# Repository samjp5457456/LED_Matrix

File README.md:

# LED_Matrix
Repo for all files used in the LED Matrix project. This includes hardware files (schematics, Gerbers, and CAD files...) as well as software (GUI and functional code).

Created by Eleanor Taylor for the LED Matrix senior project (fall 2023) at UCCS.

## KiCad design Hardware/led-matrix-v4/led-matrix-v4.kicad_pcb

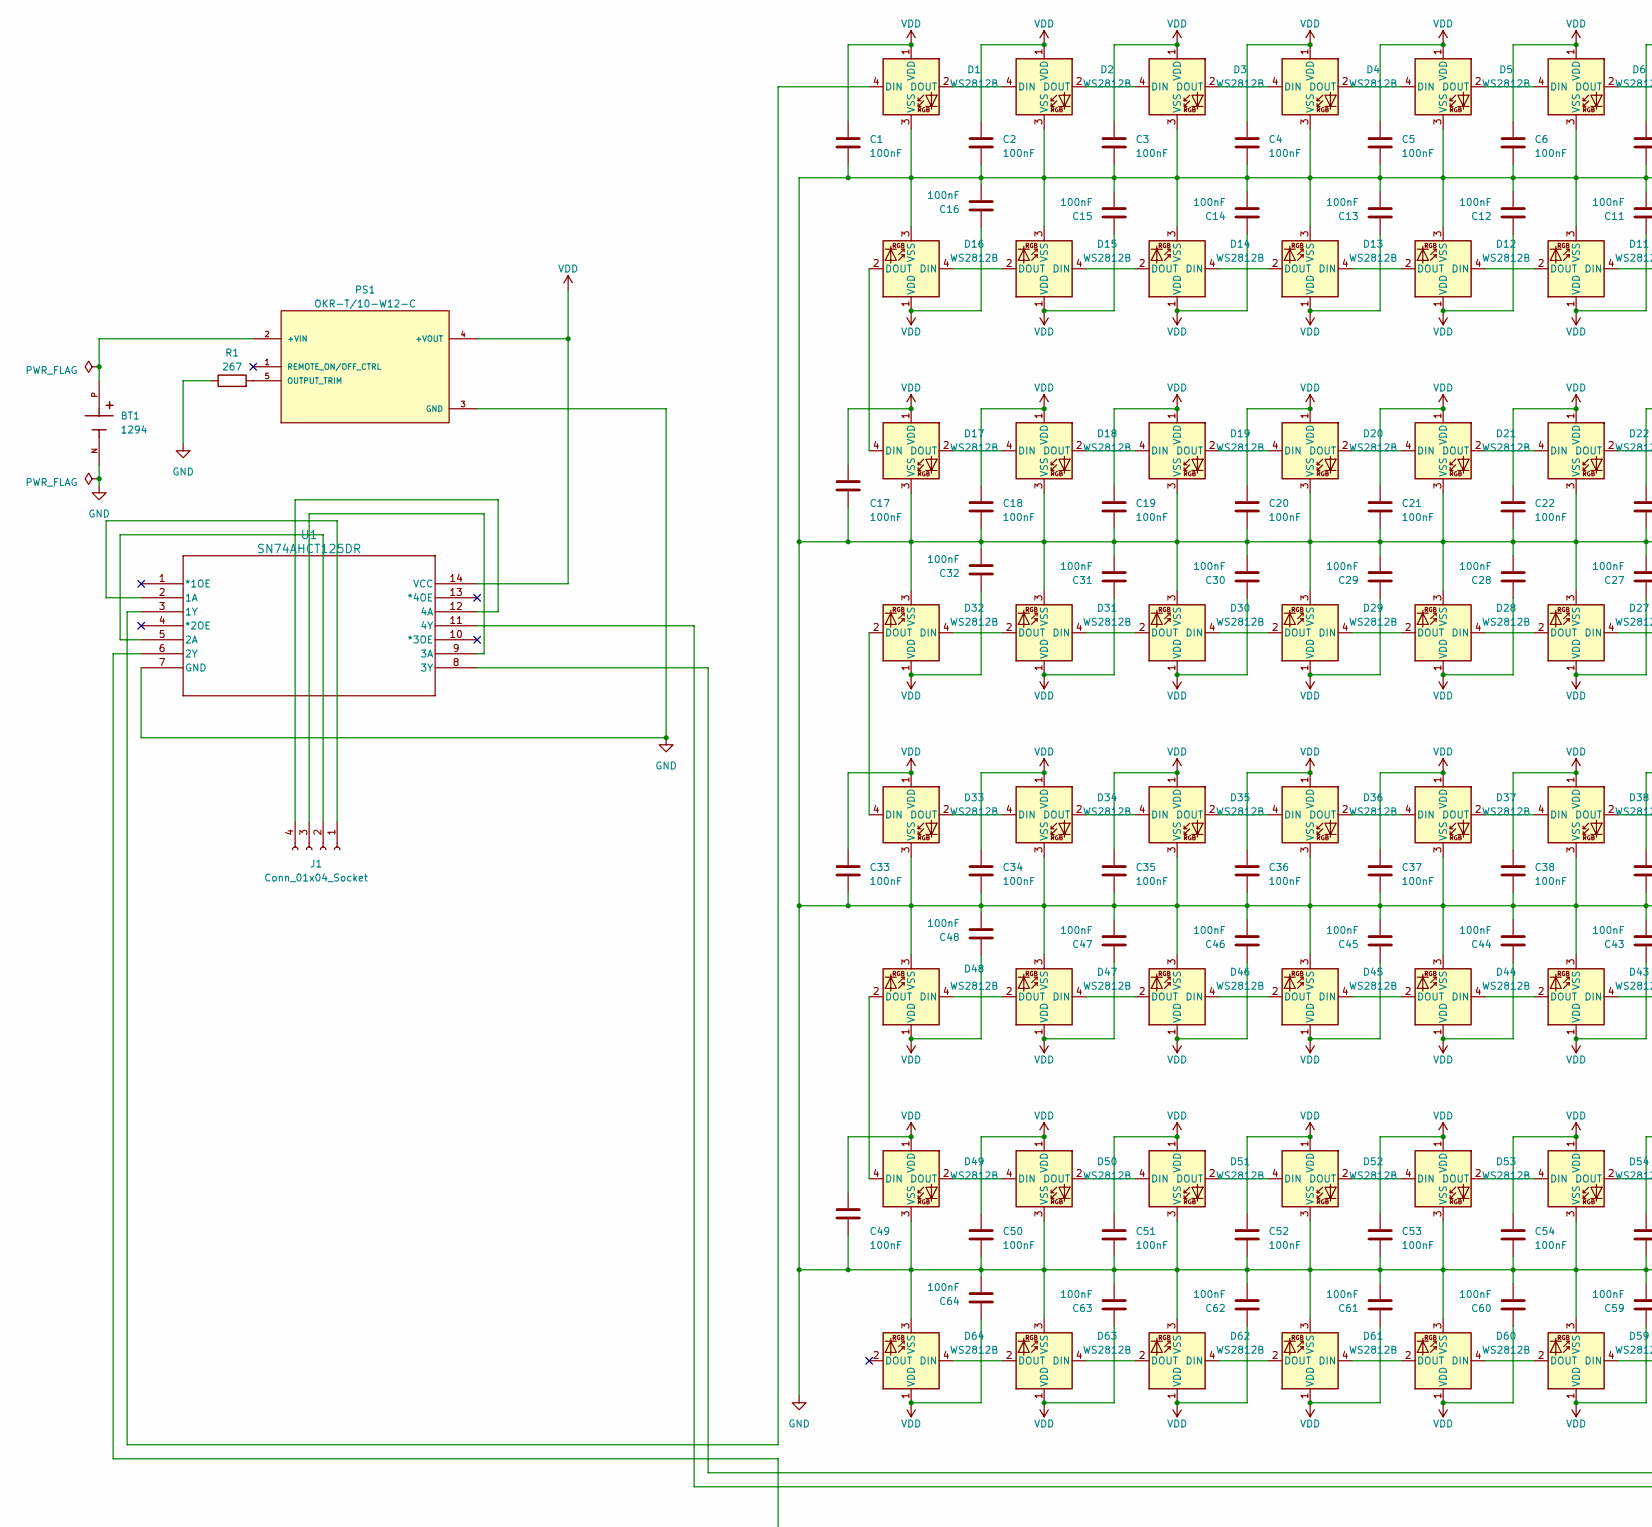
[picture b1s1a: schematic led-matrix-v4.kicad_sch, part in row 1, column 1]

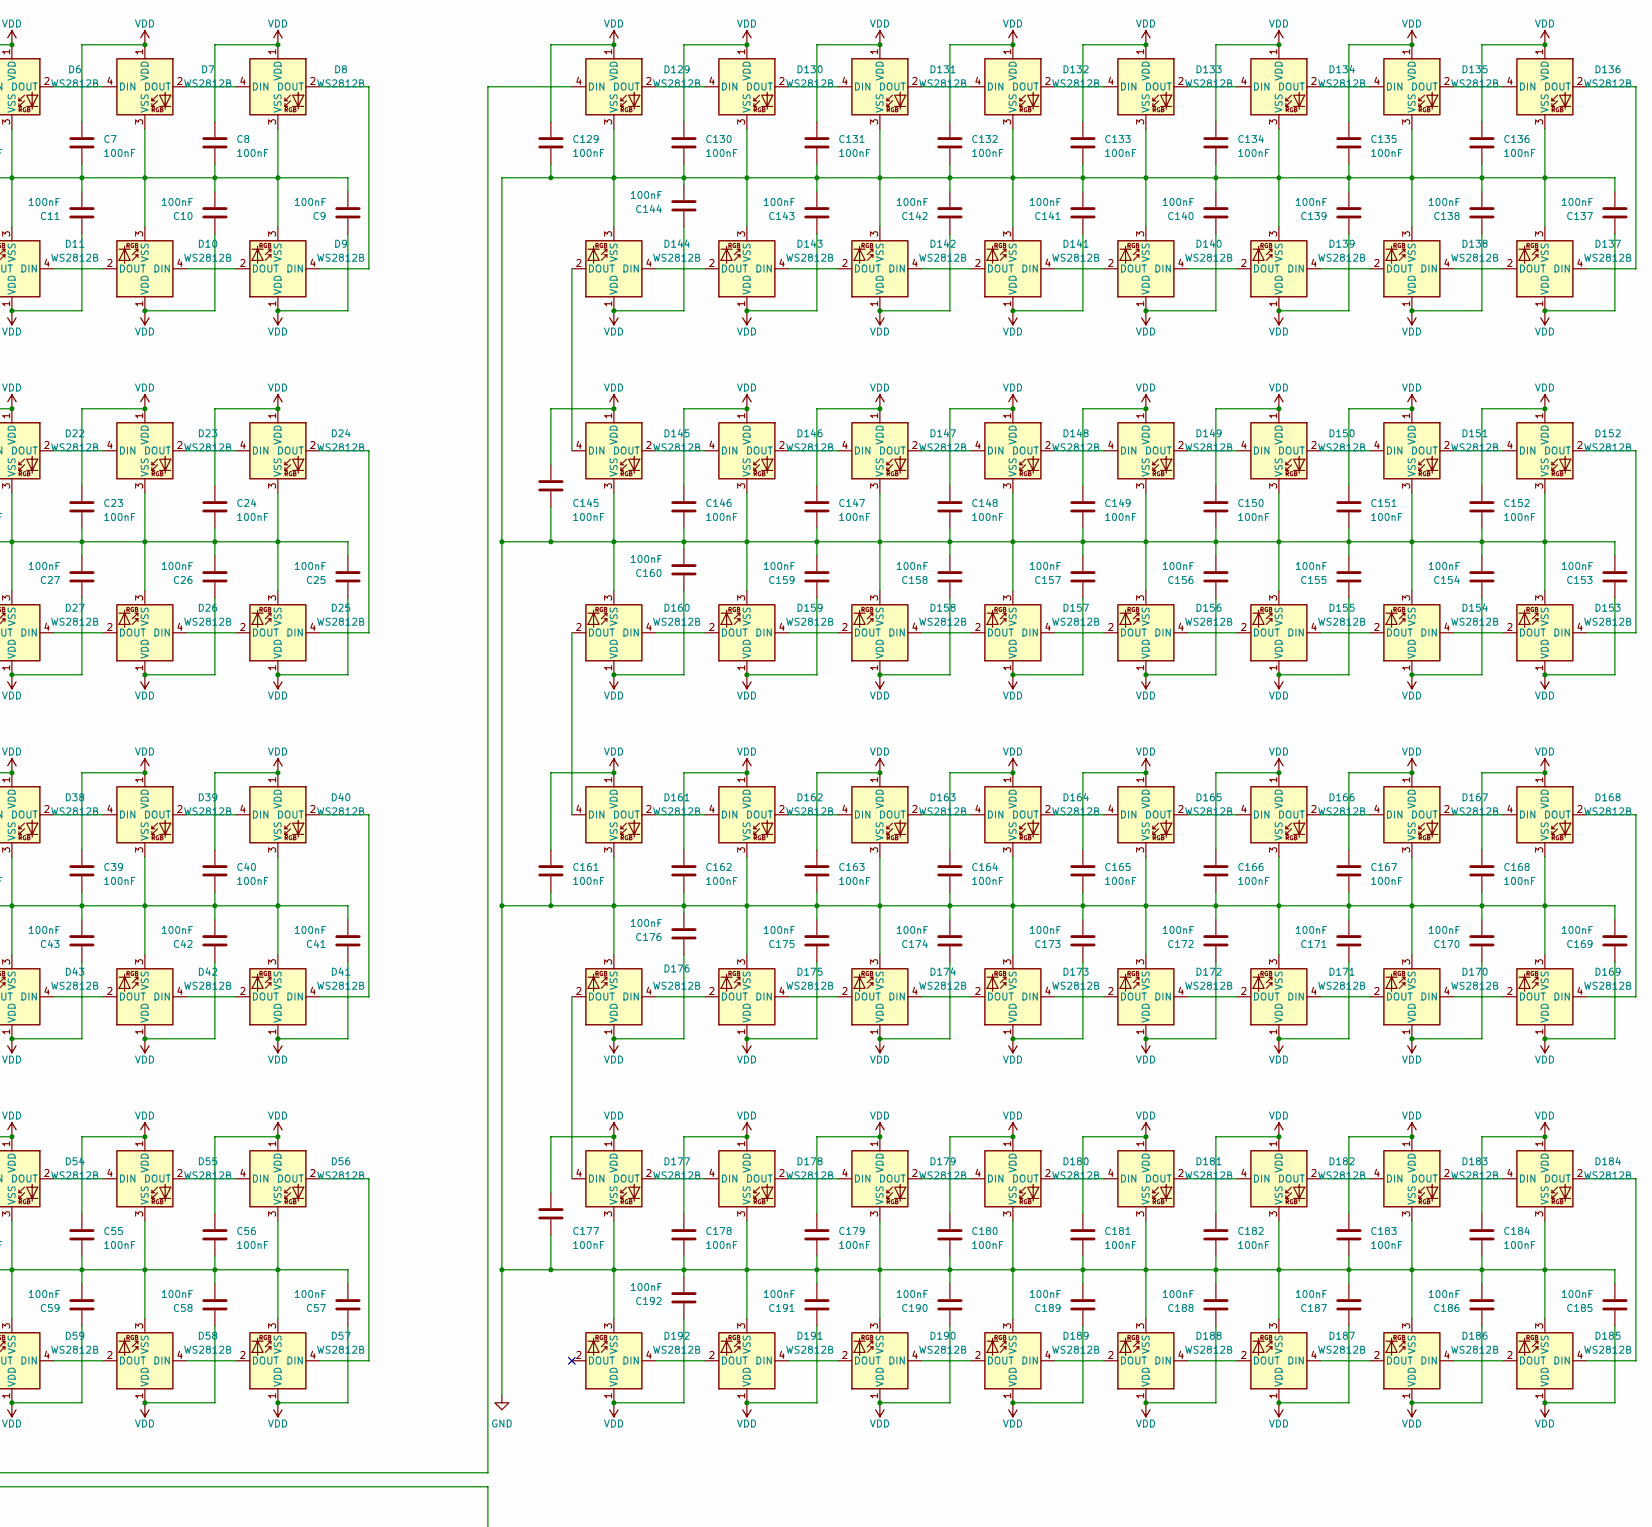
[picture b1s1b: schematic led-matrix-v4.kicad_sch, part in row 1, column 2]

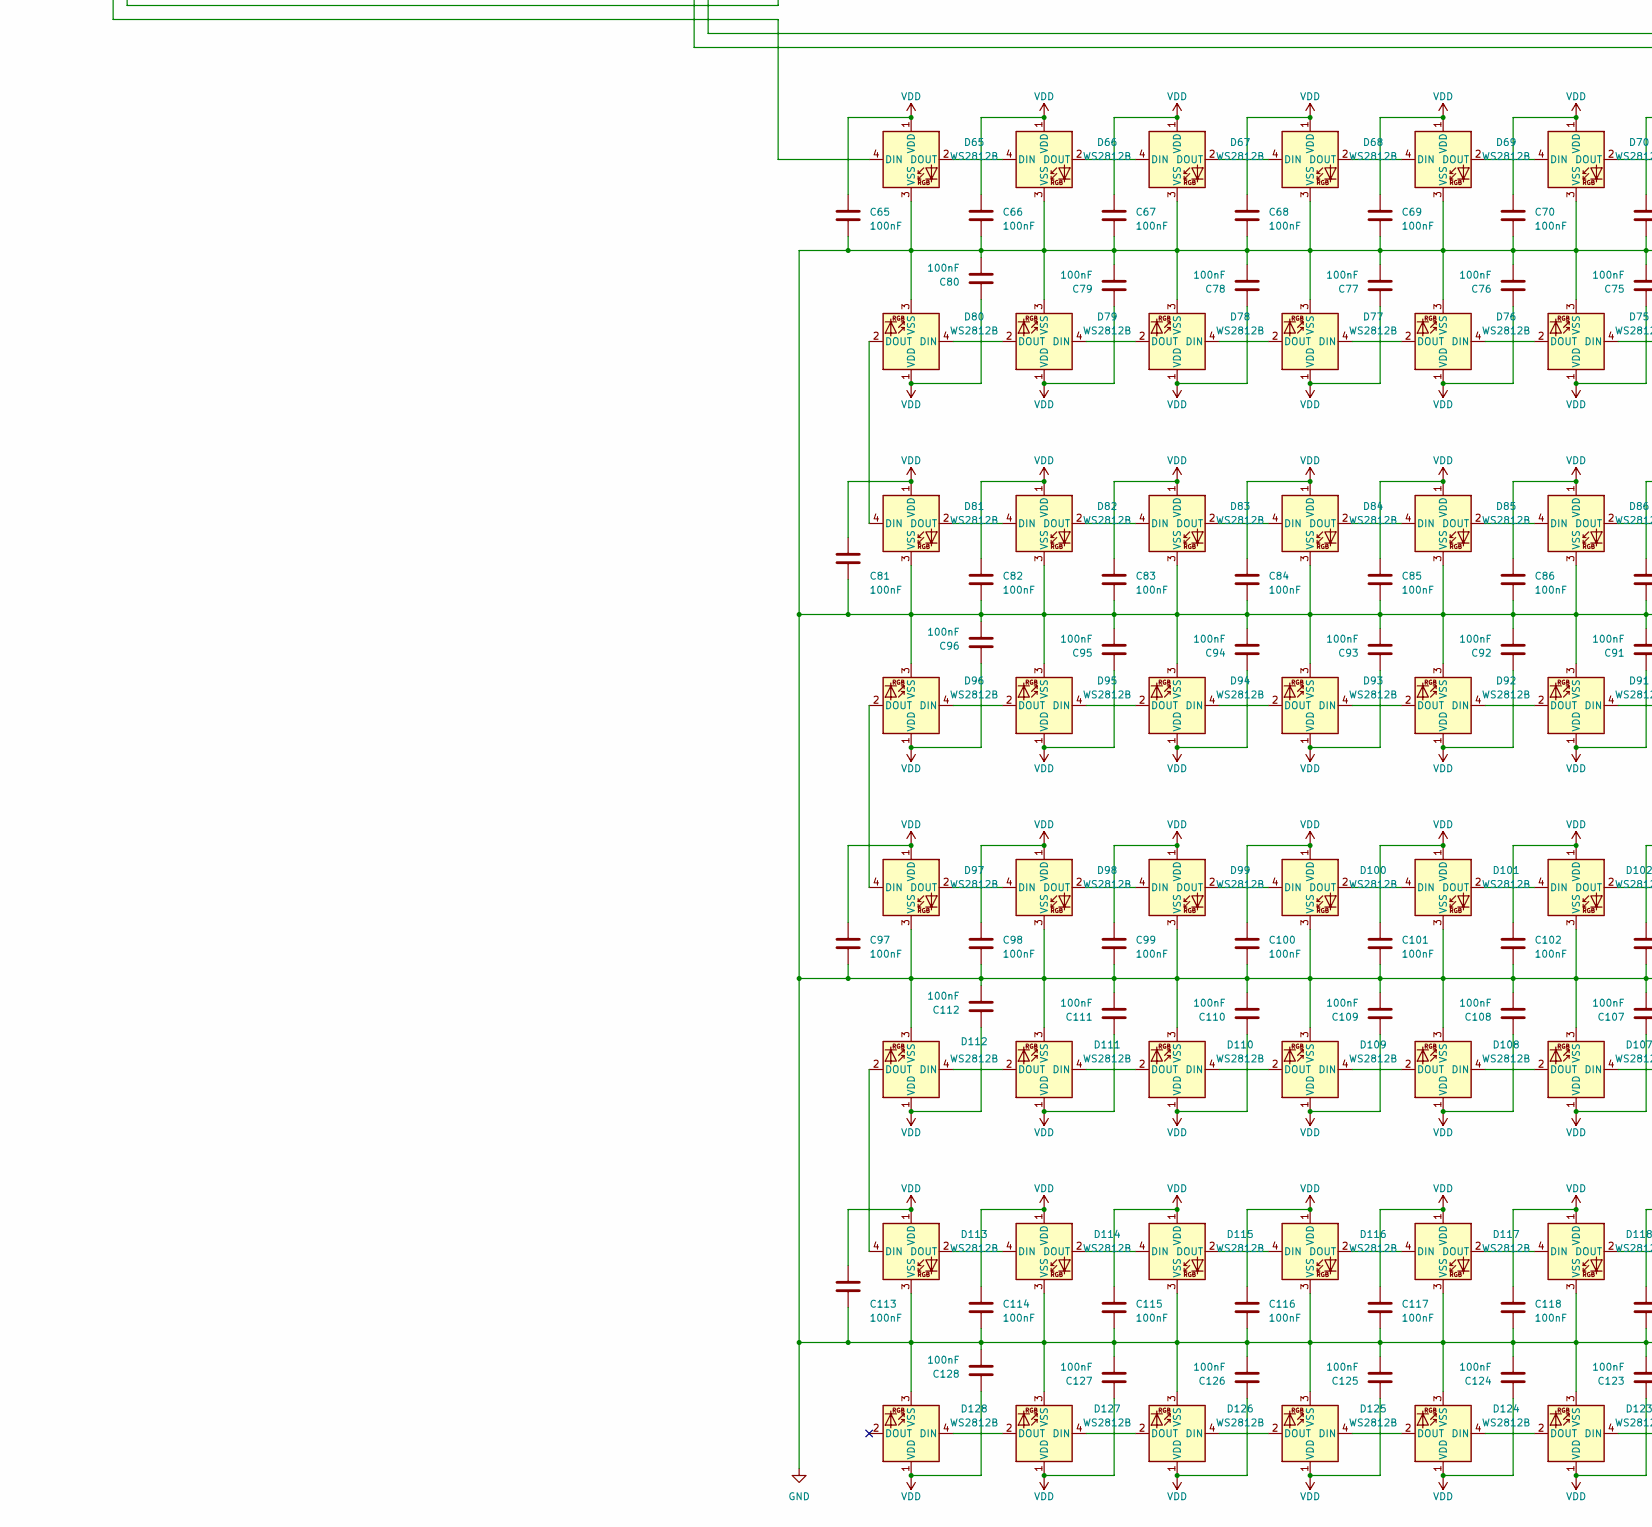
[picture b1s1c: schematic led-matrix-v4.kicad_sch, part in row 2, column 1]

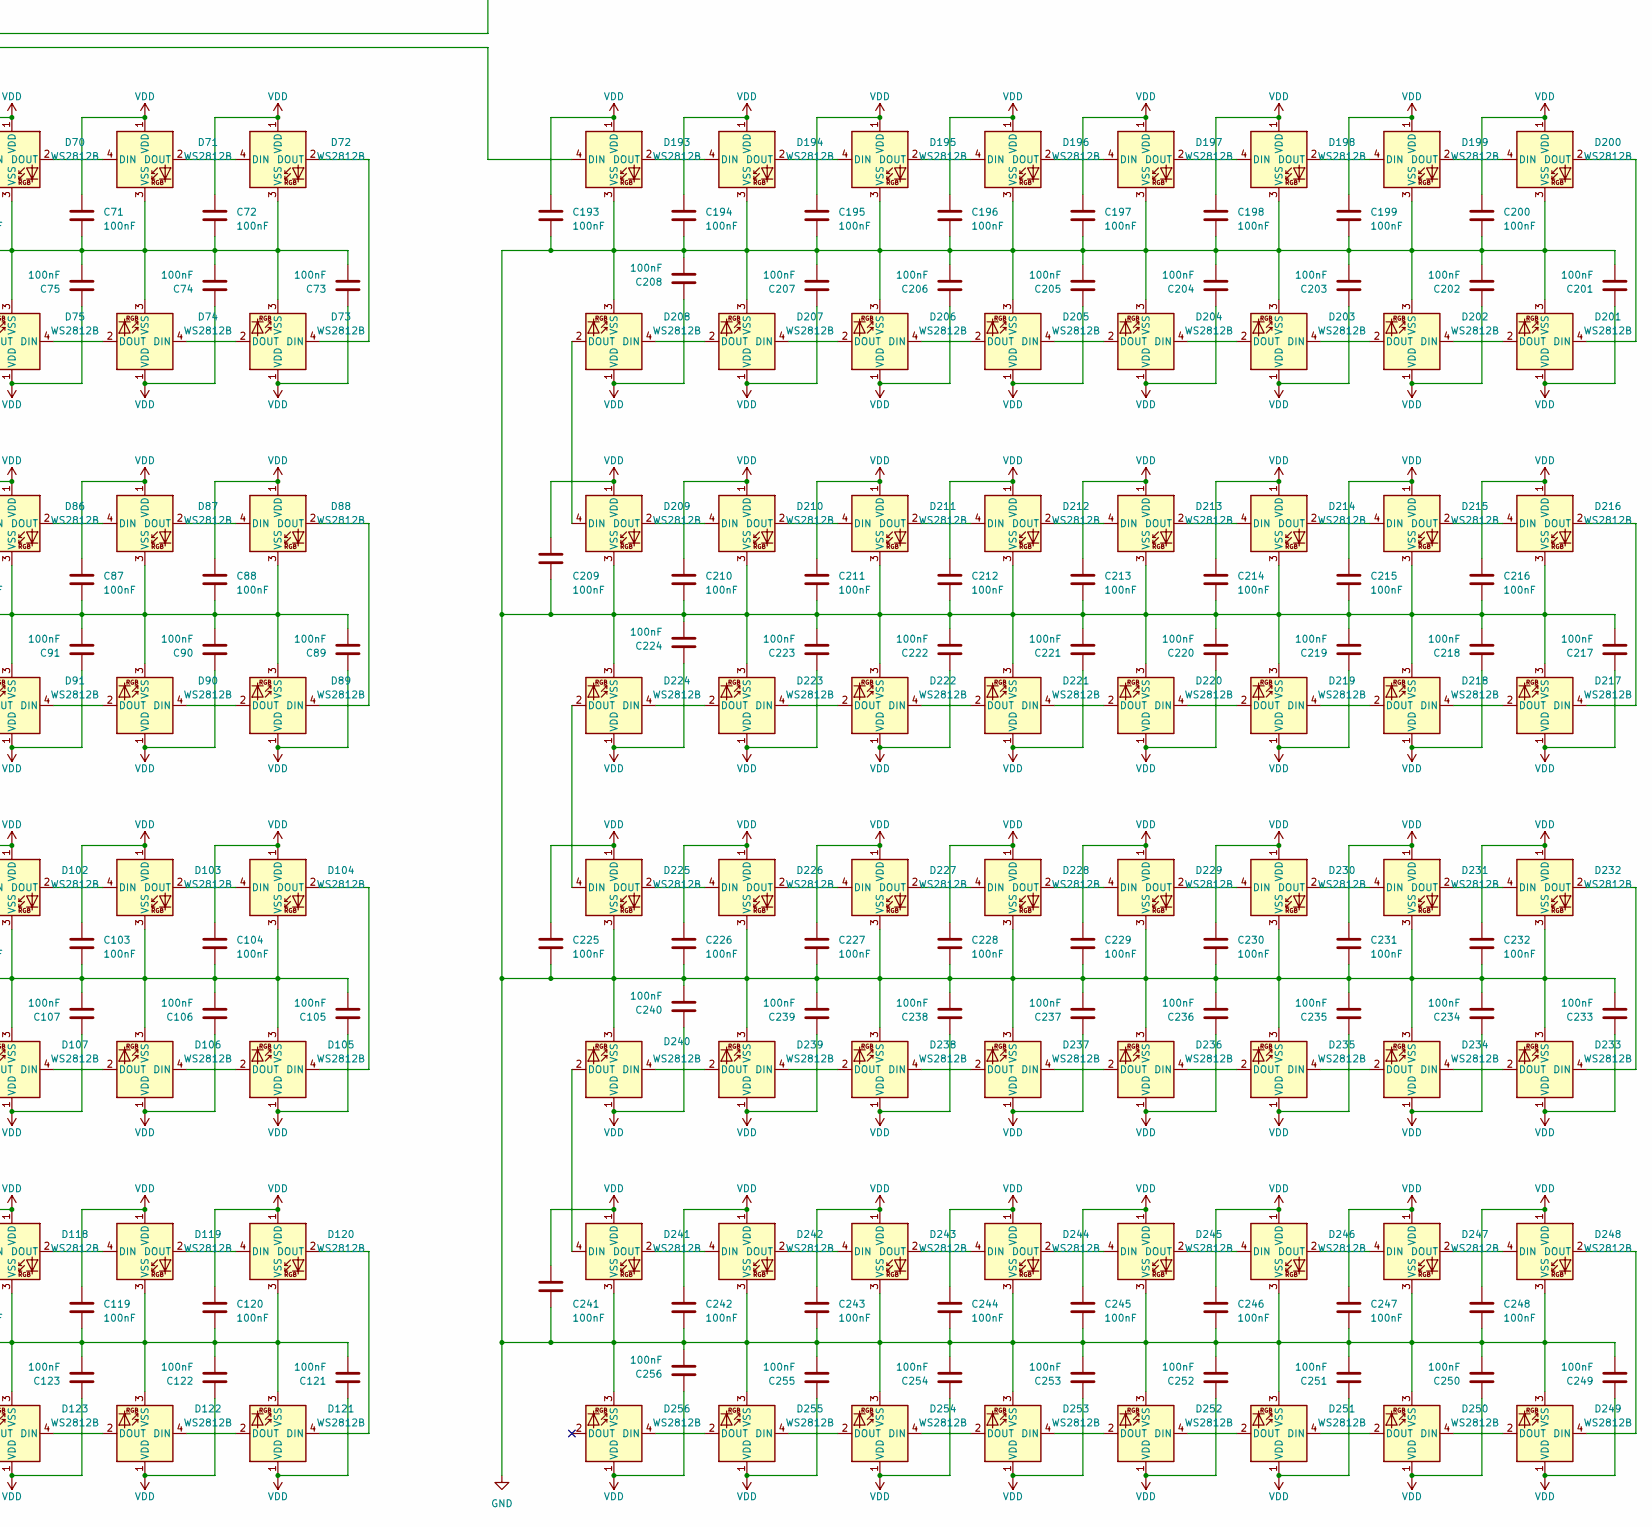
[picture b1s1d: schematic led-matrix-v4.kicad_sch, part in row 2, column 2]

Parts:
BT1: 1294; BAT_1294; PARTREV C
C1, C2, C3, C4, C5, C6, C7, C8, C9, C10, C11, C12, C13, C14, C15, C16, C17, C18, C19, C20, C21, C22, C23, C24, C25, C26, C27, C28, C29, C30, C31, C32, C33, C34, C35, C36, C37, C38, C39, C40, C41, C42, C43, C44, C45, C46, C47, C48, C49, C50, C51, C52, C53, C54, C55, C56, C57, C58, C59, C60, C61, C62, C63, C64, C65, C66, C67, C68, C69, C70, C71, C72, C73, C74, C75, C76, C77, C78, C79, C80, C81, C82, C83, C84, C85, C86, C87, C88, C89, C90, C91, C92, C93, C94, C95, C96, C97, C98, C99, C100, C101, C102, C103, C104, C105, C106, C107, C108, C109, C110, C111, C112, C113, C114, C115, C116, C117, C118, C119, C120, C121, C122, C123, C124, C125, C126, C127, C128, C129, C130, C131, C132, C133, C134, C135, C136, C137, C138, C139, C140, C141, C142, C143, C144, C145, C146, C147, C148, C149, C150, C151, C152, C153, C154, C155, C156, C157, C158, C159, C160, C161, C162, C163, C164, C165, C166, C167, C168, C169, C170, C171, C172, C173, C174, C175, C176, C177, C178, C179, C180, C181, C182, C183, C184, C185, C186, C187, C188, C189, C190, C191, C192, C193, C194, C195, C196, C197, C198, C199, C200, C201, C202, C203, C204, C205, C206, C207, C208, C209, C210, C211, C212, C213, C214, C215, C216, C217, C218, C219, C220, C221, C222, C223, C224, C225, C226, C227, C228, C229, C230, C231, C232, C233, C234, C235, C236, C237, C238, C239, C240, C241, C242, C243, C244, C245, C246, C247, C248, C249, C250, C251, C252, C253, C254, C255, C256: 100nF; C_0805_2012Metric
D1, D2, D3, D4, D5, D6, D7, D8, D9, D10, D11, D12, D13, D14, D15, D16, D17, D18, D19, D20, D21, D22, D23, D24, D25, D26, D27, D28, D29, D30, D31, D32, D33, D34, D35, D36, D37, D38, D39, D40, D41, D42, D43, D44, D45, D46, D47, D48, D49, D50, D51, D52, D53, D54, D55, D56, D57, D58, D59, D60, D61, D62, D63, D64, D65, D66, D67, D68, D69, D70, D71, D72, D73, D74, D75, D76, D77, D78, D79, D80, D81, D82, D83, D84, D85, D86, D87, D88, D89, D90, D91, D92, D93, D94, D95, D96, D97, D98, D99, D100, D101, D102, D103, D104, D105, D106, D107, D108, D109, D110, D111, D112, D113, D114, D115, D116, D117, D118, D119, D120, D121, D122, D123, D124, D125, D126, D127, D128, D129, D130, D131, D132, D133, D134, D135, D136, D137, D138, D139, D140, D141, D142, D143, D144, D145, D146, D147, D148, D149, D150, D151, D152, D153, D154, D155, D156, D157, D158, D159, D160, D161, D162, D163, D164, D165, D166, D167, D168, D169, D170, D171, D172, D173, D174, D175, D176, D177, D178, D179, D180, D181, D182, D183, D184, D185, D186, D187, D188, D189, D190, D191, D192, D193, D194, D195, D196, D197, D198, D199, D200, D201, D202, D203, D204, D205, D206, D207, D208, D209, D210, D211, D212, D213, D214, D215, D216, D217, D218, D219, D220, D221, D222, D223, D224, D225, D226, D227, D228, D229, D230, D231, D232, D233, D234, D235, D236, D237, D238, D239, D240, D241, D242, D243, D244, D245, D246, D247, D248, D249, D250, D251, D252, D253, D254, D255, D256: WS2812B; LED_WS2812B_PLCC4_5.0x5.0mm_P3.2mm
J1: Conn_01x04_Socket; PinHeader_1x04_P2.54mm_Vertical
PS1: OKR-T/10-W12-C; CONV_OKR-T_10-W12-C
R1: 267; R_0805_2012Metric
U1: SN74AHCT125DR; D14

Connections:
GND: BT1.N, C1.2, C2.2, C3.2, C4.2, C5.2, C6.2, C7.2, C8.2, C9.2, C10.2, C11.2, C12.2, C13.2, C14.2, C15.2, C16.2, C17.2, C18.2, C19.2, C20.2, C21.2, C22.2, C23.2, C24.2, C25.2, C26.2, C27.2, C28.2, C29.2, C30.2, C31.2, C32.2, C33.2, C34.2, C35.2, C36.2, C37.2, C38.2, C39.2, C40.2, C41.2, C42.2, C43.2, C44.2, C45.2, C46.2, C47.2, C48.2, C49.2, C50.2, C51.2, C52.2, C53.2, C54.2, C55.2, C56.2, C57.2, C58.2, C59.2, C60.2, C61.2, C62.2, C63.2, C64.2, C65.2, C66.2, C67.2, C68.2, C69.2, C70.2, C71.2, C72.2, C73.2, C74.2, C75.2, C76.2, C77.2, C78.2, C79.2, C80.2, C81.2, C82.2, C83.2, C84.2, C85.2, C86.2, C87.2, C88.2, C89.2, C90.2, C91.2, C92.2, C93.2, C94.2, C95.2, C96.2, C97.2, C98.2, C99.2, C100.2, C101.2, C102.2, C103.2, C104.2, C105.2, C106.2, C107.2, C108.2, C109.2, C110.2, C111.2, C112.2, C113.2, C114.2, C115.2, C116.2, C117.2, C118.2, C119.2, C120.2, C121.2, C122.2, C123.2, C124.2, C125.2, C126.2, C127.2, C128.2, C129.2, C130.2, C131.2, C132.2, C133.2, C134.2, C135.2, C136.2, C137.2, C138.2, C139.2, C140.2, C141.2, C142.2, C143.2, C144.2, C145.2, C146.2, C147.2, C148.2, C149.2, C150.2, C151.2, C152.2, C153.2, C154.2, C155.2, C156.2, C157.2, C158.2, C159.2, C160.2, C161.2, C162.2, C163.2, C164.2, C165.2, C166.2, C167.2, C168.2, C169.2, C170.2, C171.2, C172.2, C173.2, C174.2, C175.2, C176.2, C177.2, C178.2, C179.2, C180.2, C181.2, C182.2, C183.2, C184.2, C185.2, C186.2, C187.2, C188.2, C189.2, C190.2, C191.2, C192.2, C193.2, C194.2, C195.2, C196.2, C197.2, C198.2, C199.2, C200.2, C201.2, C202.2, C203.2, C204.2, C205.2, C206.2, C207.2, C208.2, C209.2, C210.2, C211.2, C212.2, C213.2, C214.2, C215.2, C216.2, C217.2, C218.2, C219.2, C220.2, C221.2, C222.2, C223.2, C224.2, C225.2, C226.2, C227.2, C228.2, C229.2, C230.2, C231.2, C232.2, C233.2, C234.2, C235.2, C236.2, C237.2, C238.2, C239.2, C240.2, C241.2, C242.2, C243.2, C244.2, C245.2, C246.2, C247.2, C248.2, C249.2, C250.2, C251.2, C252.2, C253.2, C254.2, C255.2, C256.2, D1.3 (VSS), D2.3 (VSS), D3.3 (VSS), D4.3 (VSS), D5.3 (VSS), D6.3 (VSS), D7.3 (VSS), D8.3 (VSS), D9.3 (VSS), D10.3 (VSS), D11.3 (VSS), D12.3 (VSS), D13.3 (VSS), D14.3 (VSS), D15.3 (VSS), D16.3 (VSS), D17.3 (VSS), D18.3 (VSS), D19.3 (VSS), D20.3 (VSS), D21.3 (VSS), D22.3 (VSS), D23.3 (VSS), D24.3 (VSS), D25.3 (VSS), D26.3 (VSS), D27.3 (VSS), D28.3 (VSS), D29.3 (VSS), D30.3 (VSS), D31.3 (VSS), D32.3 (VSS), D33.3 (VSS), D34.3 (VSS), D35.3 (VSS), D36.3 (VSS), D37.3 (VSS), D38.3 (VSS), D39.3 (VSS), D40.3 (VSS), D41.3 (VSS), D42.3 (VSS), D43.3 (VSS), D44.3 (VSS), D45.3 (VSS), D46.3 (VSS), D47.3 (VSS), D48.3 (VSS), D49.3 (VSS), D50.3 (VSS), D51.3 (VSS), D52.3 (VSS), D53.3 (VSS), D54.3 (VSS), D55.3 (VSS), D56.3 (VSS), D57.3 (VSS), D58.3 (VSS), D59.3 (VSS), D60.3 (VSS), D61.3 (VSS), D62.3 (VSS), D63.3 (VSS), D64.3 (VSS), D65.3 (VSS), D66.3 (VSS), D67.3 (VSS), D68.3 (VSS), D69.3 (VSS), D70.3 (VSS), D71.3 (VSS), D72.3 (VSS), D73.3 (VSS), D74.3 (VSS), D75.3 (VSS), D76.3 (VSS), D77.3 (VSS)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
unnamed: D1.4 (DIN), U1.3 (1Y)
unnamed: D1.2 (DOUT), D2.4 (DIN)
unnamed: D2.2 (DOUT), D3.4 (DIN)
unnamed: D3.2 (DOUT), D4.4 (DIN)
unnamed: D4.2 (DOUT), D5.4 (DIN)
unnamed: D5.2 (DOUT), D6.4 (DIN)
unnamed: D6.2 (DOUT), D7.4 (DIN)
unnamed: D7.2 (DOUT), D8.4 (DIN)
unnamed: D8.2 (DOUT), D9.4 (DIN)
unnamed: D9.2 (DOUT), D10.4 (DIN)
unnamed: D10.2 (DOUT), D11.4 (DIN)
unnamed: D11.2 (DOUT), D12.4 (DIN)
unnamed: D12.2 (DOUT), D13.4 (DIN)
unnamed: D13.2 (DOUT), D14.4 (DIN)
unnamed: D14.2 (DOUT), D15.4 (DIN)
unnamed: D15.2 (DOUT), D16.4 (DIN)
unnamed: D16.2 (DOUT), D17.4 (DIN)
unnamed: D17.2 (DOUT), D18.4 (DIN)
unnamed: D18.2 (DOUT), D19.4 (DIN)
unnamed: D19.2 (DOUT), D20.4 (DIN)
unnamed: D20.2 (DOUT), D21.4 (DIN)
unnamed: D21.2 (DOUT), D22.4 (DIN)
unnamed: D22.2 (DOUT), D23.4 (DIN)
unnamed: D23.2 (DOUT), D24.4 (DIN)
unnamed: D24.2 (DOUT), D25.4 (DIN)
unnamed: D25.2 (DOUT), D26.4 (DIN)
unnamed: D26.2 (DOUT), D27.4 (DIN)
unnamed: D27.2 (DOUT), D28.4 (DIN)
unnamed: D28.2 (DOUT), D29.4 (DIN)
unnamed: D29.2 (DOUT), D30.4 (DIN)
unnamed: D30.2 (DOUT), D31.4 (DIN)
unnamed: D31.2 (DOUT), D32.4 (DIN)
unnamed: D32.2 (DOUT), D33.4 (DIN)
unnamed: D33.2 (DOUT), D34.4 (DIN)
unnamed: D34.2 (DOUT), D35.4 (DIN)
unnamed: D35.2 (DOUT), D36.4 (DIN)
unnamed: D36.2 (DOUT), D37.4 (DIN)
unnamed: D37.2 (DOUT), D38.4 (DIN)
unnamed: D38.2 (DOUT), D39.4 (DIN)
unnamed: D39.2 (DOUT), D40.4 (DIN)
unnamed: D40.2 (DOUT), D41.4 (DIN)
unnamed: D41.2 (DOUT), D42.4 (DIN)
unnamed: D42.2 (DOUT), D43.4 (DIN)
unnamed: D43.2 (DOUT), D44.4 (DIN)
unnamed: D44.2 (DOUT), D45.4 (DIN)
unnamed: D45.2 (DOUT), D46.4 (DIN)
unnamed: D46.2 (DOUT), D47.4 (DIN)
unnamed: D47.2 (DOUT), D48.4 (DIN)
unnamed: D48.2 (DOUT), D49.4 (DIN)
unnamed: D49.2 (DOUT), D50.4 (DIN)
unnamed: D50.2 (DOUT), D51.4 (DIN)
unnamed: D51.2 (DOUT), D52.4 (DIN)
unnamed: D52.2 (DOUT), D53.4 (DIN)
unnamed: D53.2 (DOUT), D54.4 (DIN)
unnamed: D54.2 (DOUT), D55.4 (DIN)
unnamed: D55.2 (DOUT), D56.4 (DIN)
unnamed: D56.2 (DOUT), D57.4 (DIN)
unnamed: D57.2 (DOUT), D58.4 (DIN)
unnamed: D58.2 (DOUT), D59.4 (DIN)
unnamed: D59.2 (DOUT), D60.4 (DIN)
unnamed: D60.2 (DOUT), D61.4 (DIN)
unnamed: D61.2 (DOUT), D62.4 (DIN)
unnamed: D62.2 (DOUT), D63.4 (DIN)
unnamed: D63.2 (DOUT), D64.4 (DIN)
unnamed: D65.4 (DIN), U1.6 (2Y)
unnamed: D65.2 (DOUT), D66.4 (DIN)
unnamed: D66.2 (DOUT), D67.4 (DIN)
unnamed: D67.2 (DOUT), D68.4 (DIN)
unnamed: D68.2 (DOUT), D69.4 (DIN)
unnamed: D69.2 (DOUT), D70.4 (DIN)
unnamed: D70.2 (DOUT), D71.4 (DIN)
unnamed: D71.2 (DOUT), D72.4 (DIN)
unnamed: D72.2 (DOUT), D73.4 (DIN)
unnamed: D73.2 (DOUT), D74.4 (DIN)
unnamed: D74.2 (DOUT), D75.4 (DIN)
unnamed: D75.2 (DOUT), D76.4 (DIN)
unnamed: D76.2 (DOUT), D77.4 (DIN)
unnamed: D77.2 (DOUT), D78.4 (DIN)
unnamed: D78.2 (DOUT), D79.4 (DIN)
unnamed: D79.2 (DOUT), D80.4 (DIN)
unnamed: D80.2 (DOUT), D81.4 (DIN)
unnamed: D81.2 (DOUT), D82.4 (DIN)
unnamed: D82.2 (DOUT), D83.4 (DIN)
unnamed: D83.2 (DOUT), D84.4 (DIN)
unnamed: D84.2 (DOUT), D85.4 (DIN)
unnamed: D85.2 (DOUT), D86.4 (DIN)
unnamed: D86.2 (DOUT), D87.4 (DIN)
unnamed: D87.2 (DOUT), D88.4 (DIN)
unnamed: D88.2 (DOUT), D89.4 (DIN)
unnamed: D89.2 (DOUT), D90.4 (DIN)
unnamed: D90.2 (DOUT), D91.4 (DIN)
unnamed: D91.2 (DOUT), D92.4 (DIN)
unnamed: D92.2 (DOUT), D93.4 (DIN)
unnamed: D93.2 (DOUT), D94.4 (DIN)
unnamed: D94.2 (DOUT), D95.4 (DIN)
unnamed: D95.2 (DOUT), D96.4 (DIN)
unnamed: D96.2 (DOUT), D97.4 (DIN)
unnamed: D97.2 (DOUT), D98.4 (DIN)
unnamed: D98.2 (DOUT), D99.4 (DIN)
unnamed: D99.2 (DOUT), D100.4 (DIN)
unnamed: D100.2 (DOUT), D101.4 (DIN)
unnamed: D101.2 (DOUT), D102.4 (DIN)
unnamed: D102.2 (DOUT), D103.4 (DIN)
unnamed: D103.2 (DOUT), D104.4 (DIN)
unnamed: D104.2 (DOUT), D105.4 (DIN)
unnamed: D105.2 (DOUT), D106.4 (DIN)
unnamed: D106.2 (DOUT), D107.4 (DIN)
unnamed: D107.2 (DOUT), D108.4 (DIN)
unnamed: D108.2 (DOUT), D109.4 (DIN)
unnamed: D109.2 (DOUT), D110.4 (DIN)
unnamed: D110.2 (DOUT), D111.4 (DIN)
unnamed: D111.2 (DOUT), D112.4 (DIN)
unnamed: D112.2 (DOUT), D113.4 (DIN)
unnamed: D113.2 (DOUT), D114.4 (DIN)
unnamed: D114.2 (DOUT), D115.4 (DIN)
unnamed: D115.2 (DOUT), D116.4 (DIN)
unnamed: D116.2 (DOUT), D117.4 (DIN)
unnamed: D117.2 (DOUT), D118.4 (DIN)
unnamed: D118.2 (DOUT), D119.4 (DIN)
unnamed: D119.2 (DOUT), D120.4 (DIN)
unnamed: D120.2 (DOUT), D121.4 (DIN)
unnamed: D121.2 (DOUT), D122.4 (DIN)
unnamed: D122.2 (DOUT), D123.4 (DIN)
unnamed: D123.2 (DOUT), D124.4 (DIN)
unnamed: D124.2 (DOUT), D125.4 (DIN)
unnamed: D125.2 (DOUT), D126.4 (DIN)
unnamed: D126.2 (DOUT), D127.4 (DIN)
unnamed: D127.2 (DOUT), D128.4 (DIN)
unnamed: D129.4 (DIN), U1.8 (3Y)
unnamed: D129.2 (DOUT), D130.4 (DIN)
unnamed: D130.2 (DOUT), D131.4 (DIN)
unnamed: D131.2 (DOUT), D132.4 (DIN)
unnamed: D132.2 (DOUT), D133.4 (DIN)
unnamed: D133.2 (DOUT), D134.4 (DIN)
unnamed: D134.2 (DOUT), D135.4 (DIN)
unnamed: D135.2 (DOUT), D136.4 (DIN)
unnamed: D136.2 (DOUT), D137.4 (DIN)
unnamed: D137.2 (DOUT), D138.4 (DIN)
unnamed: D138.2 (DOUT), D139.4 (DIN)
unnamed: D139.2 (DOUT), D140.4 (DIN)
unnamed: D140.2 (DOUT), D141.4 (DIN)
unnamed: D141.2 (DOUT), D142.4 (DIN)
unnamed: D142.2 (DOUT), D143.4 (DIN)
unnamed: D143.2 (DOUT), D144.4 (DIN)
unnamed: D144.2 (DOUT), D145.4 (DIN)
unnamed: D145.2 (DOUT), D146.4 (DIN)
unnamed: D146.2 (DOUT), D147.4 (DIN)
unnamed: D147.2 (DOUT), D148.4 (DIN)
unnamed: D148.2 (DOUT), D149.4 (DIN)
unnamed: D149.2 (DOUT), D150.4 (DIN)
unnamed: D150.2 (DOUT), D151.4 (DIN)
unnamed: D151.2 (DOUT), D152.4 (DIN)
unnamed: D152.2 (DOUT), D153.4 (DIN)
unnamed: D153.2 (DOUT), D154.4 (DIN)
unnamed: D154.2 (DOUT), D155.4 (DIN)
unnamed: D155.2 (DOUT), D156.4 (DIN)
unnamed: D156.2 (DOUT), D157.4 (DIN)
unnamed: D157.2 (DOUT), D158.4 (DIN)
unnamed: D158.2 (DOUT), D159.4 (DIN)
unnamed: D159.2 (DOUT), D160.4 (DIN)
unnamed: D160.2 (DOUT), D161.4 (DIN)
unnamed: D161.2 (DOUT), D162.4 (DIN)
unnamed: D162.2 (DOUT), D163.4 (DIN)
unnamed: D163.2 (DOUT), D164.4 (DIN)
unnamed: D164.2 (DOUT), D165.4 (DIN)
unnamed: D165.2 (DOUT), D166.4 (DIN)
unnamed: D166.2 (DOUT), D167.4 (DIN)
unnamed: D167.2 (DOUT), D168.4 (DIN)
unnamed: D168.2 (DOUT), D169.4 (DIN)
unnamed: D169.2 (DOUT), D170.4 (DIN)
unnamed: D170.2 (DOUT), D171.4 (DIN)
unnamed: D171.2 (DOUT), D172.4 (DIN)
unnamed: D172.2 (DOUT), D173.4 (DIN)
unnamed: D173.2 (DOUT), D174.4 (DIN)
unnamed: D174.2 (DOUT), D175.4 (DIN)
unnamed: D175.2 (DOUT), D176.4 (DIN)
unnamed: D176.2 (DOUT), D177.4 (DIN)
unnamed: D177.2 (DOUT), D178.4 (DIN)
unnamed: D178.2 (DOUT), D179.4 (DIN)
unnamed: D179.2 (DOUT), D180.4 (DIN)
unnamed: D180.2 (DOUT), D181.4 (DIN)
unnamed: D181.2 (DOUT), D182.4 (DIN)
unnamed: D182.2 (DOUT), D183.4 (DIN)
unnamed: D183.2 (DOUT), D184.4 (DIN)
unnamed: D184.2 (DOUT), D185.4 (DIN)
unnamed: D185.2 (DOUT), D186.4 (DIN)
unnamed: D186.2 (DOUT), D187.4 (DIN)
unnamed: D187.2 (DOUT), D188.4 (DIN)
unnamed: D188.2 (DOUT), D189.4 (DIN)
unnamed: D189.2 (DOUT), D190.4 (DIN)
unnamed: D190.2 (DOUT), D191.4 (DIN)
unnamed: D191.2 (DOUT), D192.4 (DIN)
unnamed: D193.4 (DIN), U1.11 (4Y)
unnamed: D193.2 (DOUT), D194.4 (DIN)
unnamed: D194.2 (DOUT), D195.4 (DIN)
unnamed: D195.2 (DOUT), D196.4 (DIN)
unnamed: D196.2 (DOUT), D197.4 (DIN)
unnamed: D197.2 (DOUT), D198.4 (DIN)
unnamed: D198.2 (DOUT), D199.4 (DIN)
unnamed: D199.2 (DOUT), D200.4 (DIN)
unnamed: D200.2 (DOUT), D201.4 (DIN)
unnamed: D201.2 (DOUT), D202.4 (DIN)
unnamed: D202.2 (DOUT), D203.4 (DIN)
unnamed: D203.2 (DOUT), D204.4 (DIN)
unnamed: D204.2 (DOUT), D205.4 (DIN)
unnamed: D205.2 (DOUT), D206.4 (DIN)
unnamed: D206.2 (DOUT), D207.4 (DIN)
unnamed: D207.2 (DOUT), D208.4 (DIN)
unnamed: D208.2 (DOUT), D209.4 (DIN)
unnamed: D209.2 (DOUT), D210.4 (DIN)
unnamed: D210.2 (DOUT), D211.4 (DIN)
unnamed: D211.2 (DOUT), D212.4 (DIN)
unnamed: D212.2 (DOUT), D213.4 (DIN)
unnamed: D213.2 (DOUT), D214.4 (DIN)
unnamed: D214.2 (DOUT), D215.4 (DIN)
unnamed: D215.2 (DOUT), D216.4 (DIN)
unnamed: D216.2 (DOUT), D217.4 (DIN)
unnamed: D217.2 (DOUT), D218.4 (DIN)
unnamed: D218.2 (DOUT), D219.4 (DIN)
unnamed: D219.2 (DOUT), D220.4 (DIN)
unnamed: D220.2 (DOUT), D221.4 (DIN)
unnamed: D221.2 (DOUT), D222.4 (DIN)
unnamed: D222.2 (DOUT), D223.4 (DIN)
unnamed: D223.2 (DOUT), D224.4 (DIN)
unnamed: D224.2 (DOUT), D225.4 (DIN)
unnamed: D225.2 (DOUT), D226.4 (DIN)
unnamed: D226.2 (DOUT), D227.4 (DIN)
unnamed: D227.2 (DOUT), D228.4 (DIN)
unnamed: D228.2 (DOUT), D229.4 (DIN)
unnamed: D229.2 (DOUT), D230.4 (DIN)
unnamed: D230.2 (DOUT), D231.4 (DIN)
unnamed: D231.2 (DOUT), D232.4 (DIN)
unnamed: D232.2 (DOUT), D233.4 (DIN)
unnamed: D233.2 (DOUT), D234.4 (DIN)
unnamed: D234.2 (DOUT), D235.4 (DIN)
unnamed: D235.2 (DOUT), D236.4 (DIN)
unnamed: D236.2 (DOUT), D237.4 (DIN)
unnamed: D237.2 (DOUT), D238.4 (DIN)
unnamed: D238.2 (DOUT), D239.4 (DIN)
unnamed: D239.2 (DOUT), D240.4 (DIN)
unnamed: D240.2 (DOUT), D241.4 (DIN)
unnamed: D241.2 (DOUT), D242.4 (DIN)
unnamed: D242.2 (DOUT), D243.4 (DIN)
unnamed: D243.2 (DOUT), D244.4 (DIN)
unnamed: D244.2 (DOUT), D245.4 (DIN)
unnamed: D245.2 (DOUT), D246.4 (DIN)
unnamed: D246.2 (DOUT), D247.4 (DIN)
unnamed: D247.2 (DOUT), D248.4 (DIN)
unnamed: D248.2 (DOUT), D249.4 (DIN)
unnamed: D249.2 (DOUT), D250.4 (DIN)
unnamed: D250.2 (DOUT), D251.4 (DIN)
unnamed: D251.2 (DOUT), D252.4 (DIN)
unnamed: D252.2 (DOUT), D253.4 (DIN)
unnamed: D253.2 (DOUT), D254.4 (DIN)
unnamed: D254.2 (DOUT), D255.4 (DIN)
unnamed: D255.2 (DOUT), D256.4 (DIN)
unnamed: J1.1, U1.2 (1A)
unnamed: J1.2, U1.5 (2A)
unnamed: J1.3, U1.9 (3A)
unnamed: J1.4, U1.12 (4A)
unnamed: BT1.P, PS1.2 (+VIN)
unnamed: PS1.5 (OUTPUT_TRIM), R1.2
VDD: C1.1, C2.1, C3.1, C4.1, C5.1, C6.1, C7.1, C8.1, C9.1, C10.1, C11.1, C12.1, C13.1, C14.1, C15.1, C16.1, C17.1, C18.1, C19.1, C20.1, C21.1, C22.1, C23.1, C24.1, C25.1, C26.1, C27.1, C28.1, C29.1, C30.1, C31.1, C32.1, C33.1, C34.1, C35.1, C36.1, C37.1, C38.1, C39.1, C40.1, C41.1, C42.1, C43.1, C44.1, C45.1, C46.1, C47.1, C48.1, C49.1, C50.1, C51.1, C52.1, C53.1, C54.1, C55.1, C56.1, C57.1, C58.1, C59.1, C60.1, C61.1, C62.1, C63.1, C64.1, C65.1, C66.1, C67.1, C68.1, C69.1, C70.1, C71.1, C72.1, C73.1, C74.1, C75.1, C76.1, C77.1, C78.1, C79.1, C80.1, C81.1, C82.1, C83.1, C84.1, C85.1, C86.1, C87.1, C88.1, C89.1, C90.1, C91.1, C92.1, C93.1, C94.1, C95.1, C96.1, C97.1, C98.1, C99.1, C100.1, C101.1, C102.1, C103.1, C104.1, C105.1, C106.1, C107.1, C108.1, C109.1, C110.1, C111.1, C112.1, C113.1, C114.1, C115.1, C116.1, C117.1, C118.1, C119.1, C120.1, C121.1, C122.1, C123.1, C124.1, C125.1, C126.1, C127.1, C128.1, C129.1, C130.1, C131.1, C132.1, C133.1, C134.1, C135.1, C136.1, C137.1, C138.1, C139.1, C140.1, C141.1, C142.1, C143.1, C144.1, C145.1, C146.1, C147.1, C148.1, C149.1, C150.1, C151.1, C152.1, C153.1, C154.1, C155.1, C156.1, C157.1, C158.1, C159.1, C160.1, C161.1, C162.1, C163.1, C164.1, C165.1, C166.1, C167.1, C168.1, C169.1, C170.1, C171.1, C172.1, C173.1, C174.1, C175.1, C176.1, C177.1, C178.1, C179.1, C180.1, C181.1, C182.1, C183.1, C184.1, C185.1, C186.1, C187.1, C188.1, C189.1, C190.1, C191.1, C192.1, C193.1, C194.1, C195.1, C196.1, C197.1, C198.1, C199.1, C200.1, C201.1, C202.1, C203.1, C204.1, C205.1, C206.1, C207.1, C208.1, C209.1, C210.1, C211.1, C212.1, C213.1, C214.1, C215.1, C216.1, C217.1, C218.1, C219.1, C220.1, C221.1, C222.1, C223.1, C224.1, C225.1, C226.1, C227.1, C228.1, C229.1, C230.1, C231.1, C232.1, C233.1, C234.1, C235.1, C236.1, C237.1, C238.1, C239.1, C240.1, C241.1, C242.1, C243.1, C244.1, C245.1, C246.1, C247.1, C248.1, C249.1, C250.1, C251.1, C252.1, C253.1, C254.1, C255.1, C256.1, D1.1 (VDD), D2.1 (VDD), D3.1 (VDD), D4.1 (VDD), D5.1 (VDD), D6.1 (VDD), D7.1 (VDD), D8.1 (VDD), D9.1 (VDD), D10.1 (VDD), D11.1 (VDD), D12.1 (VDD), D13.1 (VDD), D14.1 (VDD), D15.1 (VDD), D16.1 (VDD), D17.1 (VDD), D18.1 (VDD), D19.1 (VDD), D20.1 (VDD), D21.1 (VDD), D22.1 (VDD), D23.1 (VDD), D24.1 (VDD), D25.1 (VDD), D26.1 (VDD), D27.1 (VDD), D28.1 (VDD), D29.1 (VDD), D30.1 (VDD), D31.1 (VDD), D32.1 (VDD), D33.1 (VDD), D34.1 (VDD), D35.1 (VDD), D36.1 (VDD), D37.1 (VDD), D38.1 (VDD), D39.1 (VDD), D40.1 (VDD), D41.1 (VDD), D42.1 (VDD), D43.1 (VDD), D44.1 (VDD), D45.1 (VDD), D46.1 (VDD), D47.1 (VDD), D48.1 (VDD), D49.1 (VDD), D50.1 (VDD), D51.1 (VDD), D52.1 (VDD), D53.1 (VDD), D54.1 (VDD), D55.1 (VDD), D56.1 (VDD), D57.1 (VDD), D58.1 (VDD), D59.1 (VDD), D60.1 (VDD), D61.1 (VDD), D62.1 (VDD), D63.1 (VDD), D64.1 (VDD), D65.1 (VDD), D66.1 (VDD), D67.1 (VDD), D68.1 (VDD), D69.1 (VDD), D70.1 (VDD), D71.1 (VDD), D72.1 (VDD), D73.1 (VDD), D74.1 (VDD), D75.1 (VDD), D76.1 (VDD), D77.1 (VDD), D78.1 (VDD)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

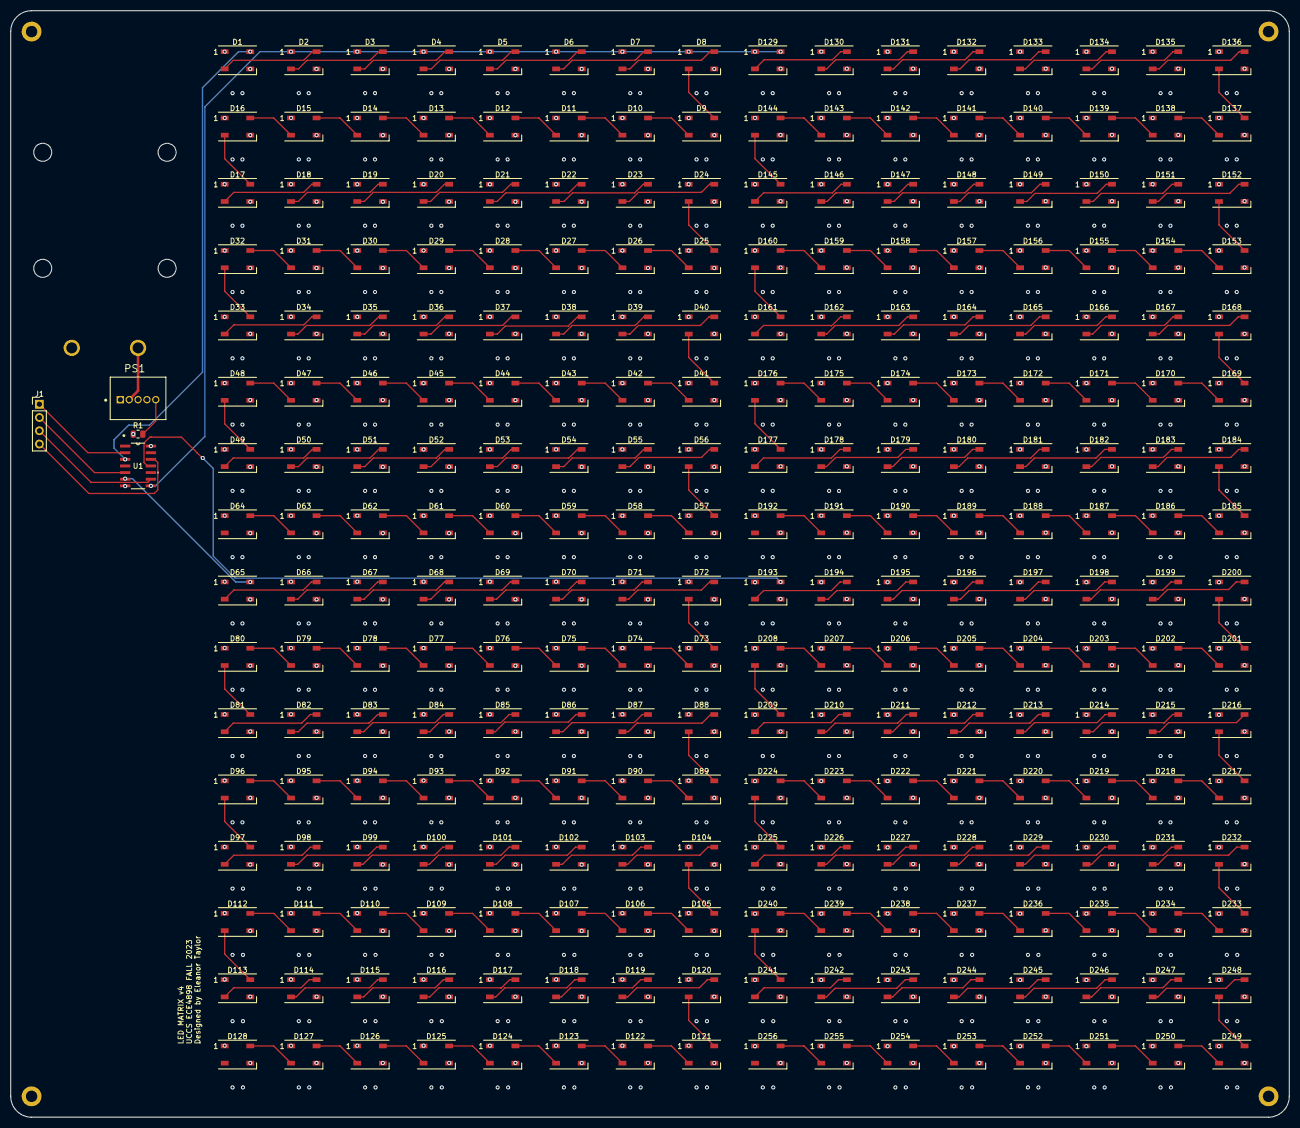
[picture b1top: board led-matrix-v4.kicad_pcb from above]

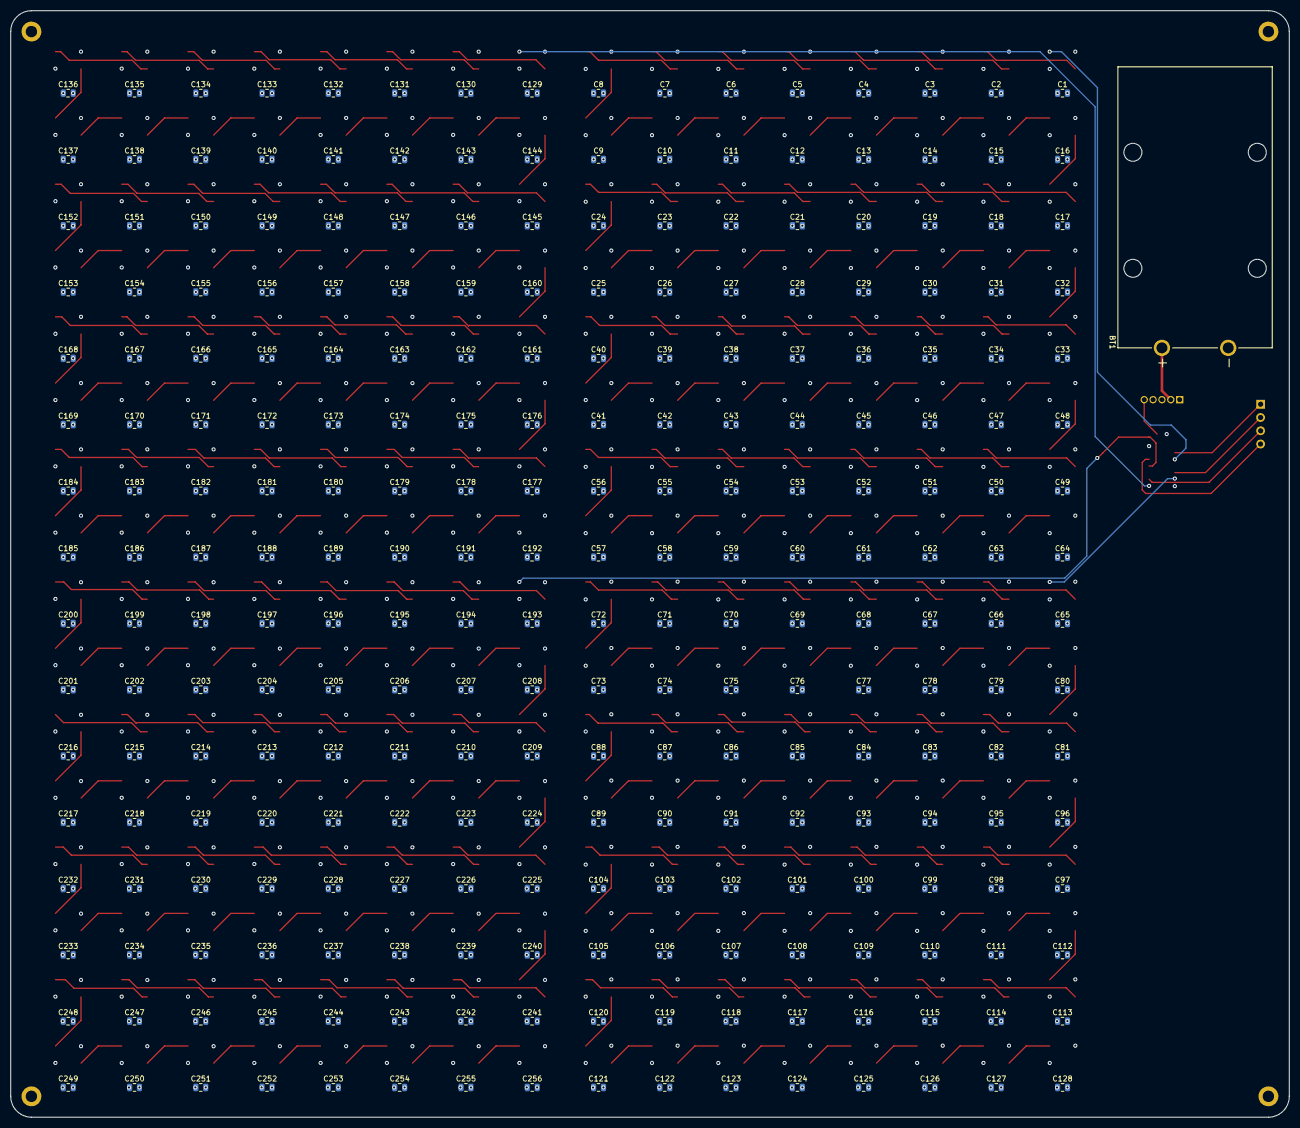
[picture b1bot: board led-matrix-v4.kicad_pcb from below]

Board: 4 copper layers, 245.0 x 212.0 mm, 517 parts (257 on the bottom side), 264 nets.

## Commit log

2023-07-13 added latest KiCad files
2023-07-13 created .gitignore file
2023-07-13 modified the gitignore file
2023-07-13 updated gitignore
2023-07-13 removed backups
2023-07-13 removed DS_Store files
2023-07-13 changed silkscreen font
2023-07-18 replaced mounting holes, filled power layers
2023-07-18 added gerbers
2023-07-18 file cleanup
2023-07-19 replaced blind vias
2023-07-19 fixed dates, etc
2023-07-21 changed jumper position on schematic for readability
2023-09-08 Added application code to software application folder
2023-09-11 added folder for next PCB iteration
2023-09-11 moved caps directly behind LEDs
2023-09-12 routed power
2023-09-15 switched to usb c from battery
2023-09-16 began routing new usb connections
2023-09-18 Forgot to add the rest of the Visual Studio solution files
2023-09-18 Updated application files
2023-09-19 Changed .NET Framework to 7.0
2023-09-20 routed LEDs
2023-09-20 version reconciliation, no change
2023-09-20 moved resistor
2023-09-21 updated buffer symbol, grounded enables
2023-09-23 minor updates
2023-09-24 finished schematics and part selection
2023-09-25 laid out, routed design
2023-09-26 minor edits
2023-09-26 refilled zones, added items to BOM
2023-09-26 finished BOm for v2
2023-09-26 Made Gerbers
2023-09-29 Hopefully updated the touchscreen issue
2023-10-03 updated backups
2023-10-03 updated backups, BOM
2023-10-04 Test Python application
2023-10-10 Create gridTest.py
    16x16 grid created and can color button black. Also have 4 color buttons on side but have not logically made them work together to change color of pixels
2023-10-10 Updated Python application that abbreviates the color button code
2023-10-11 Progress! Yayyy
2023-10-12 Added clear and erase
2023-10-12 added screengrab of pcb layout
2023-10-12 Frustrationnnnnn
2023-10-13 Update gridTest.py
    Updated erase button and clear features
